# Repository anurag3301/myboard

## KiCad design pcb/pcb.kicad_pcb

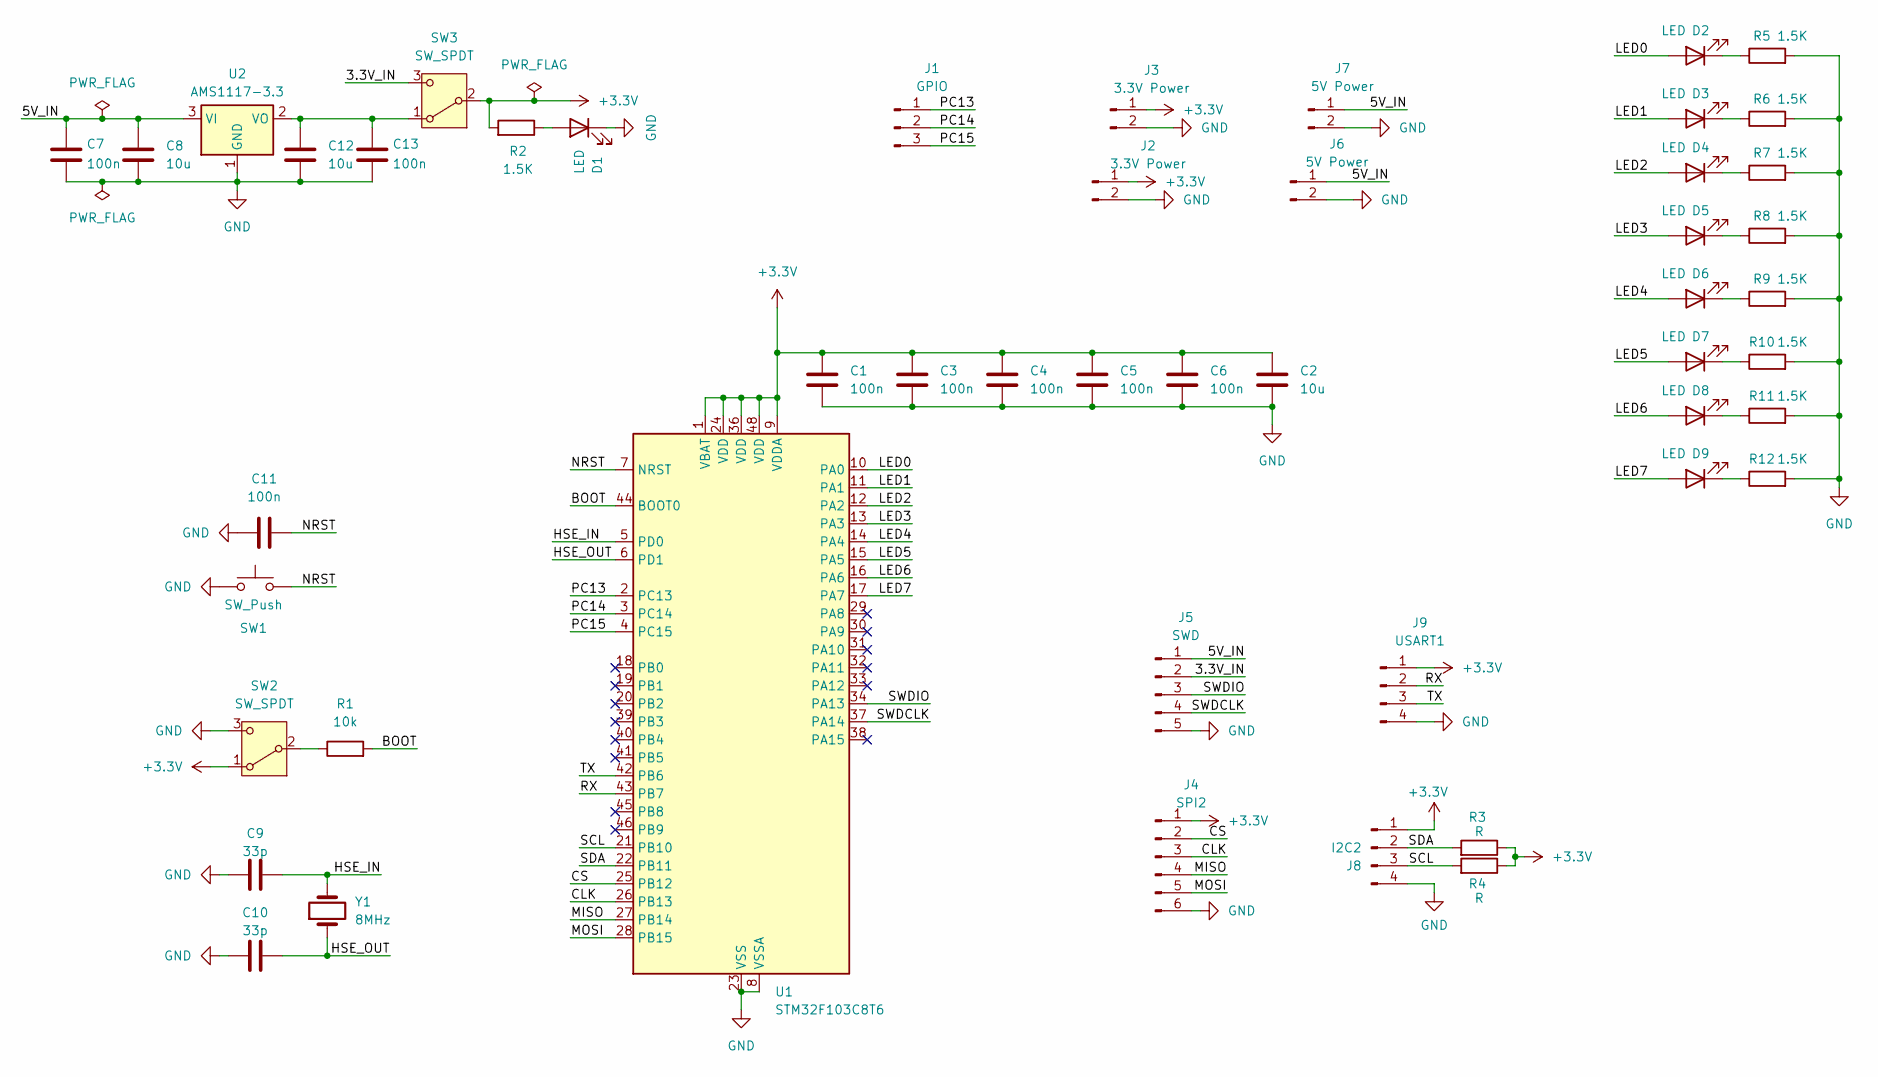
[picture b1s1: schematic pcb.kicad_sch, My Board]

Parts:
C1, C3, C4, C5, C6, C7, C11, C13: 100n; C_1206_3216Metric_Pad1.33x1.80mm_HandSolder
C2, C8, C12: 10u; C_1206_3216Metric_Pad1.33x1.80mm_HandSolder
C9, C10: 33p; C_1206_3216Metric_Pad1.33x1.80mm_HandSolder
D1, D2, D3, D4, D5, D6, D7, D8, D9: LED; LED_1206_3216Metric_Pad1.42x1.75mm_HandSolder
J1: GPIO; PinHeader_1x03_P2.54mm_Vertical
J2, J3: 3.3V Power; PinHeader_1x02_P2.54mm_Vertical
J4: SPI2; PinHeader_1x06_P2.54mm_Vertical
J5: SWD; PinHeader_1x05_P2.54mm_Vertical
J6, J7: 5V Power; PinHeader_1x02_P2.54mm_Vertical
J8: I2C2; PinHeader_1x04_P2.54mm_Vertical
J9: USART1; PinHeader_1x04_P2.54mm_Vertical
R1: 10k; R_1206_3216Metric_Pad1.30x1.75mm_HandSolder
R2, R5, R6, R7, R8, R9, R10, R11, R12: 1.5K; R_1206_3216Metric_Pad1.30x1.75mm_HandSolder
R3, R4: R; R_1206_3216Metric_Pad1.30x1.75mm_HandSolder
SW1: SW_Push; SW_SPST_PTS647_Sx38
SW2, SW3: SW_SPDT; SW_SPDT_PCM12
U1: STM32F103C8T6; LQFP-48_7x7mm_P0.5mm
U2: AMS1117-3.3; SOT-223-3_TabPin2
Y1: 8MHz; Crystal_SMD_HC49-SD

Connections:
+3.3V: C1.1, C2.1, C3.1, C4.1, C5.1, C6.1, J2.1, J3.1, J4.1, J8.1, J9.1, R2.2, R3.1, R4.1, SW2.1 (A), SW3.2 (B), U1.1 (VBAT), U1.9 (VDDA), U1.24 (VDD), U1.36 (VDD), U1.48 (VDD)
/3.3V_IN: J5.2, SW3.3 (C)
/5V_IN: C7.1, C8.1, J5.1, J6.1, J7.1, U2.3 (VI)
/BOOT: R1.2, U1.44 (BOOT0)
/CLK: J4.3, U1.26 (PB13)
/CS: J4.2, U1.25 (PB12)
/HSE_IN: C9.2, U1.5 (PD0), Y1.2
/HSE_OUT: C10.2, U1.6 (PD1), Y1.1
/LED0: D2.2 (A), U1.10 (PA0)
/LED1: D3.2 (A), U1.11 (PA1)
/LED2: D4.2 (A), U1.12 (PA2)
/LED3: D5.2 (A), U1.13 (PA3)
/LED4: D6.2 (A), U1.14 (PA4)
/LED5: D7.2 (A), U1.15 (PA5)
/LED6: D8.2 (A), U1.16 (PA6)
/LED7: D9.2 (A), U1.17 (PA7)
/MISO: J4.4, U1.27 (PB14)
/MOSI: J4.5, U1.28 (PB15)
/NRST: C11.2, SW1.2, U1.7 (NRST)
/PC13: J1.1, U1.2 (PC13)
/PC14: J1.2, U1.3 (PC14)
/PC15: J1.3, U1.4 (PC15)
/RX: J9.2, U1.43 (PB7)
/SCL: J8.3, R4.2, U1.21 (PB10)
/SDA: J8.2, R3.2, U1.22 (PB11)
/SWDCLK: J5.4, U1.37 (PA14)
/SWDIO: J5.3, U1.34 (PA13)
/TX: J9.3, U1.42 (PB6)
GND: C1.2, C2.2, C3.2, C4.2, C5.2, C6.2, C7.2, C8.2, C9.1, C10.1, C11.1, C12.2, C13.2, D1.1 (K), J2.2, J3.2, J4.6, J5.5, J6.2, J7.2, J8.4, J9.4, R5.2, R6.2, R7.2, R8.2, R9.2, R10.2, R11.2, R12.2, SW1.1, SW2.3 (C), U1.8 (VSSA), U1.23 (VSS), U1.35 (VSS), U1.47 (VSS), U2.1 (GND)
unnamed: D1.2 (A), R2.1
unnamed: D2.1 (K), R5.1
unnamed: D3.1 (K), R6.1
unnamed: D4.1 (K), R7.1
unnamed: D5.1 (K), R8.1
unnamed: D6.1 (K), R9.1
unnamed: D7.1 (K), R10.1
unnamed: D8.1 (K), R11.1
unnamed: D9.1 (K), R12.1
unnamed: R1.1, SW2.2 (B)
unnamed: C12.1, C13.1, SW3.1 (A), U2.2 (VO)

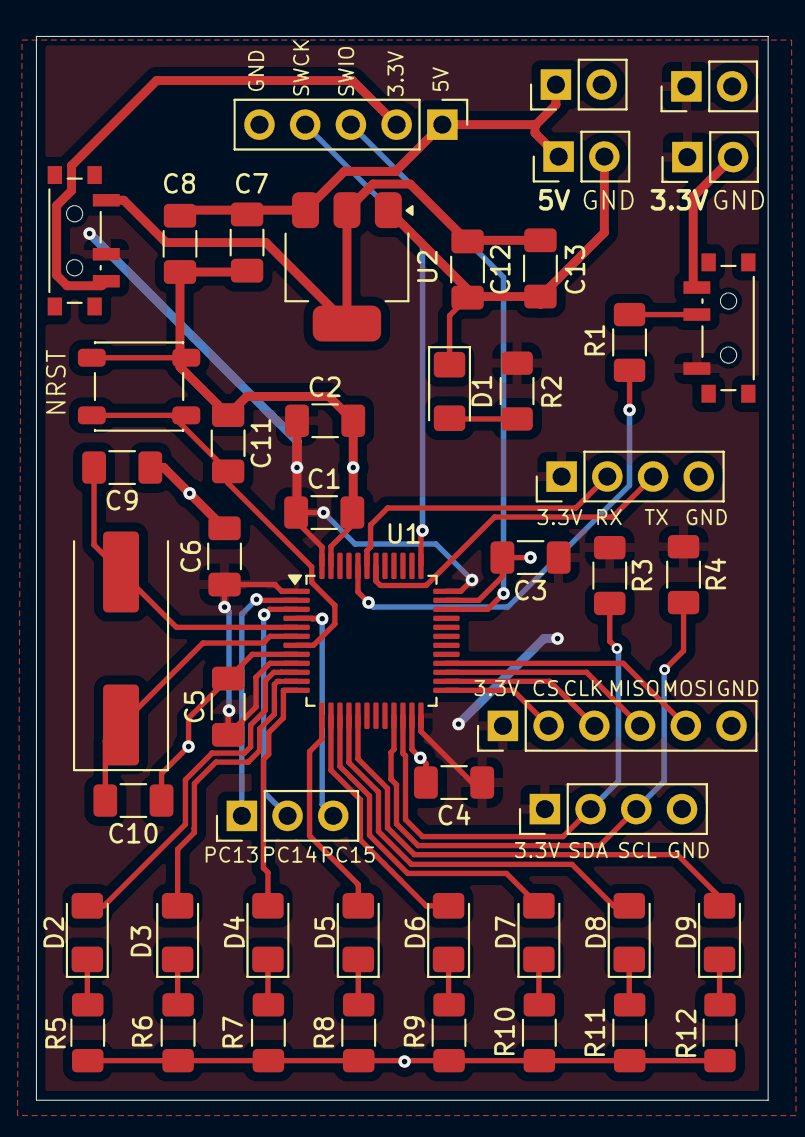
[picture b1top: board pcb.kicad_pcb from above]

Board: 2 copper layers, 40.7 x 59.1 mm, 49 parts (0 on the bottom side), 40 nets.

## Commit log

2026-01-31 STM32F103C8T6 Cube project setup
2026-02-02 Starting PCB
2026-02-03 Change kicad version to 9.0.7
2026-02-03 PCB Sync
2026-02-11 Almost done with schematics
2026-02-11 Assigned footprints
2026-02-11 Added robu PCB capabilities
2026-02-11 PCB mid-way
2026-02-11 PCB Setting done
2026-02-11 PCB almost done, proctored by Parul
2026-02-12 Completed routing with some silkscreen
2026-02-12 Finished PCB
2026-03-12 Cleaned up the schematics
2026-03-12 Using PB6 and PB7 for uart and enabled AFIO peripheral
2026-03-12 implemented _write syscall to let printf through uart
2026-03-12 I2C init code with slave scan
2026-03-13 Moved all the peripheral init code from main.c to internal.c
2026-03-13 Added gfx lib code
2026-03-13 Display code to i2c module with gfx
2026-03-17 Seperated the display init and related stuff in seperate display.c/h
2026-03-17 Font bitmap with rendering
2026-03-17 EXTI setup on PC13 and PC14
2026-03-17 Added event queue implementation
2026-03-18 SPI configuration
2026-03-18 Swapped i2c oled to spi
2026-03-19 Removed the gfx files and added gfx-mono as dependency
2026-03-19 Added gpio setup for led array and display number count
2026-03-20 codex generated html page to generate c array from bitmap canvas
